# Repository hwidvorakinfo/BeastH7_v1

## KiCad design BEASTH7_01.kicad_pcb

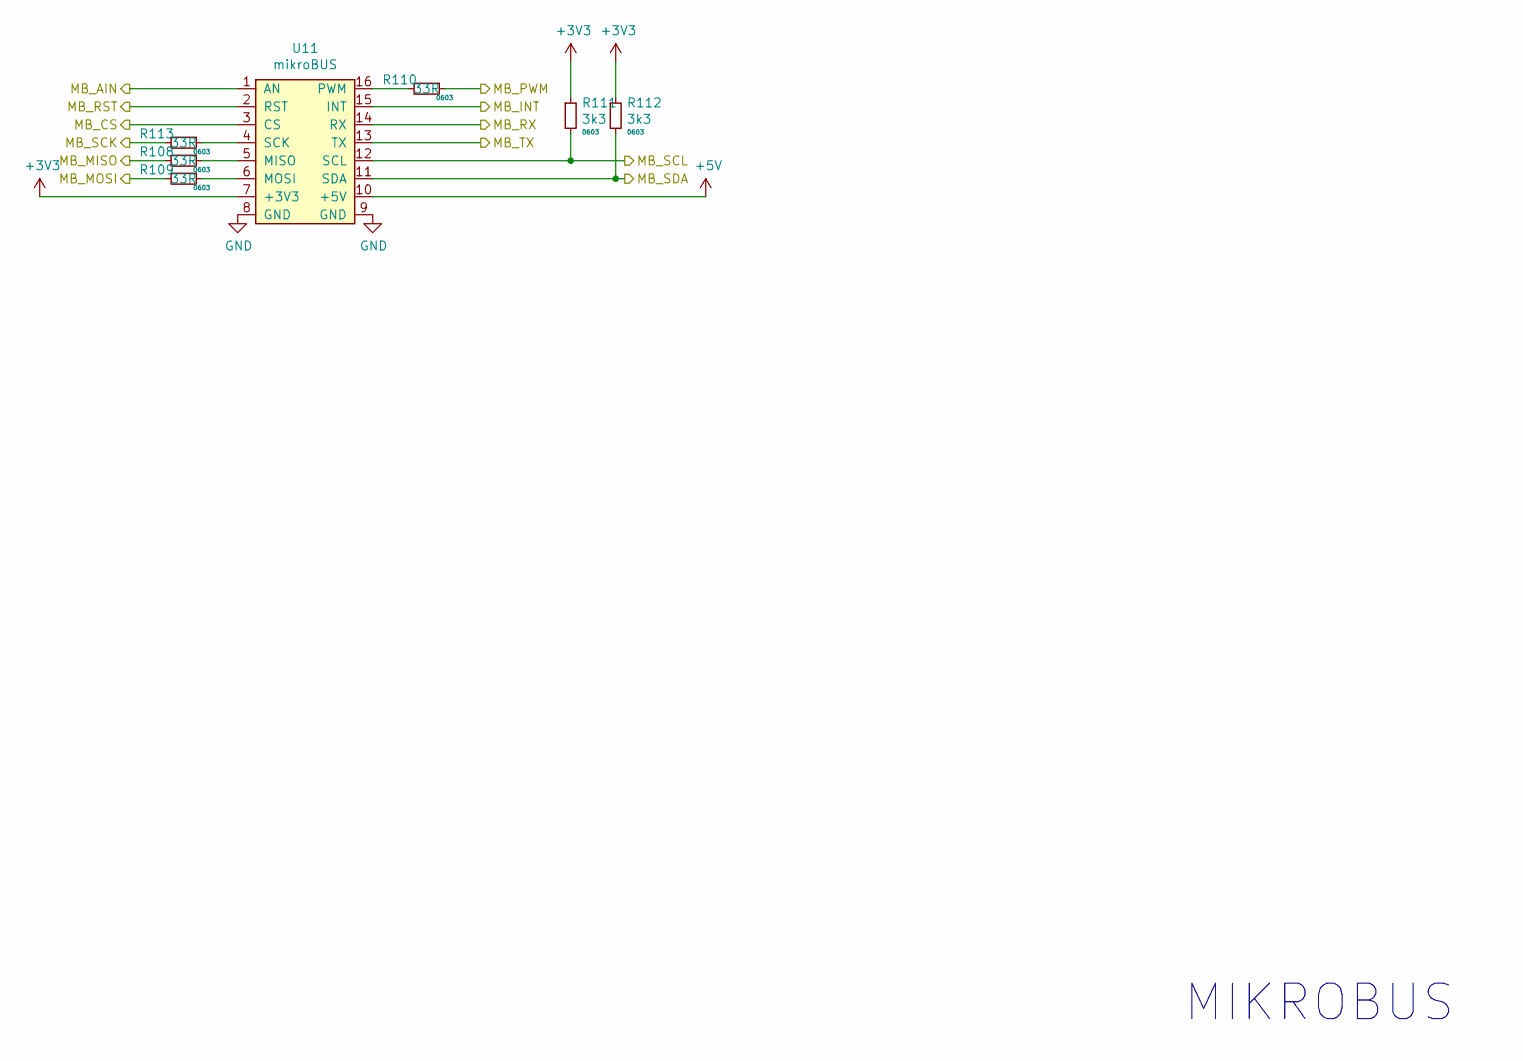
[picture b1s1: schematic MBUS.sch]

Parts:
R108, R109, R110, R113: 33R; R_0603_1608Metric
R111, R112: 3k3; R_0603_1608Metric
U11: mikroBUS

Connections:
+3V3: R111.1, R112.1, U11.7 (+3V3); also elsewhere on the board
+5V: U11.10 (+5V); also elsewhere on the board
/MCU/INPUT3: U11.1 (AN); also elsewhere on the board
/MCU/MB_CS: U11.3 (CS); also elsewhere on the board
/MCU/MB_INT: U11.15 (INT); also elsewhere on the board
/MCU/MB_MISO: R108.2; also elsewhere on the board
/MCU/MB_MOSI: R109.2; also elsewhere on the board
/MCU/MB_PWM: R110.1; also elsewhere on the board
/MCU/MB_RST: U11.2 (RST); also elsewhere on the board
/MCU/MB_RX: U11.14 (RX); also elsewhere on the board
/MCU/MB_SCK: R113.2; also elsewhere on the board
/MCU/MB_SCL: R111.2, U11.12 (SCL); also elsewhere on the board
/MCU/MB_SDA: R112.2, U11.11 (SDA); also elsewhere on the board
/MCU/MB_TX: U11.13 (TX); also elsewhere on the board
GND: U11.8 (GND), U11.9 (GND); also elsewhere on the board
unnamed: R108.1, U11.5 (MISO)
unnamed: R109.1, U11.6 (MOSI)
unnamed: R110.2, U11.16 (PWM)
unnamed: R113.1, U11.4 (SCK)

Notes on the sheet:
MIKROBUS

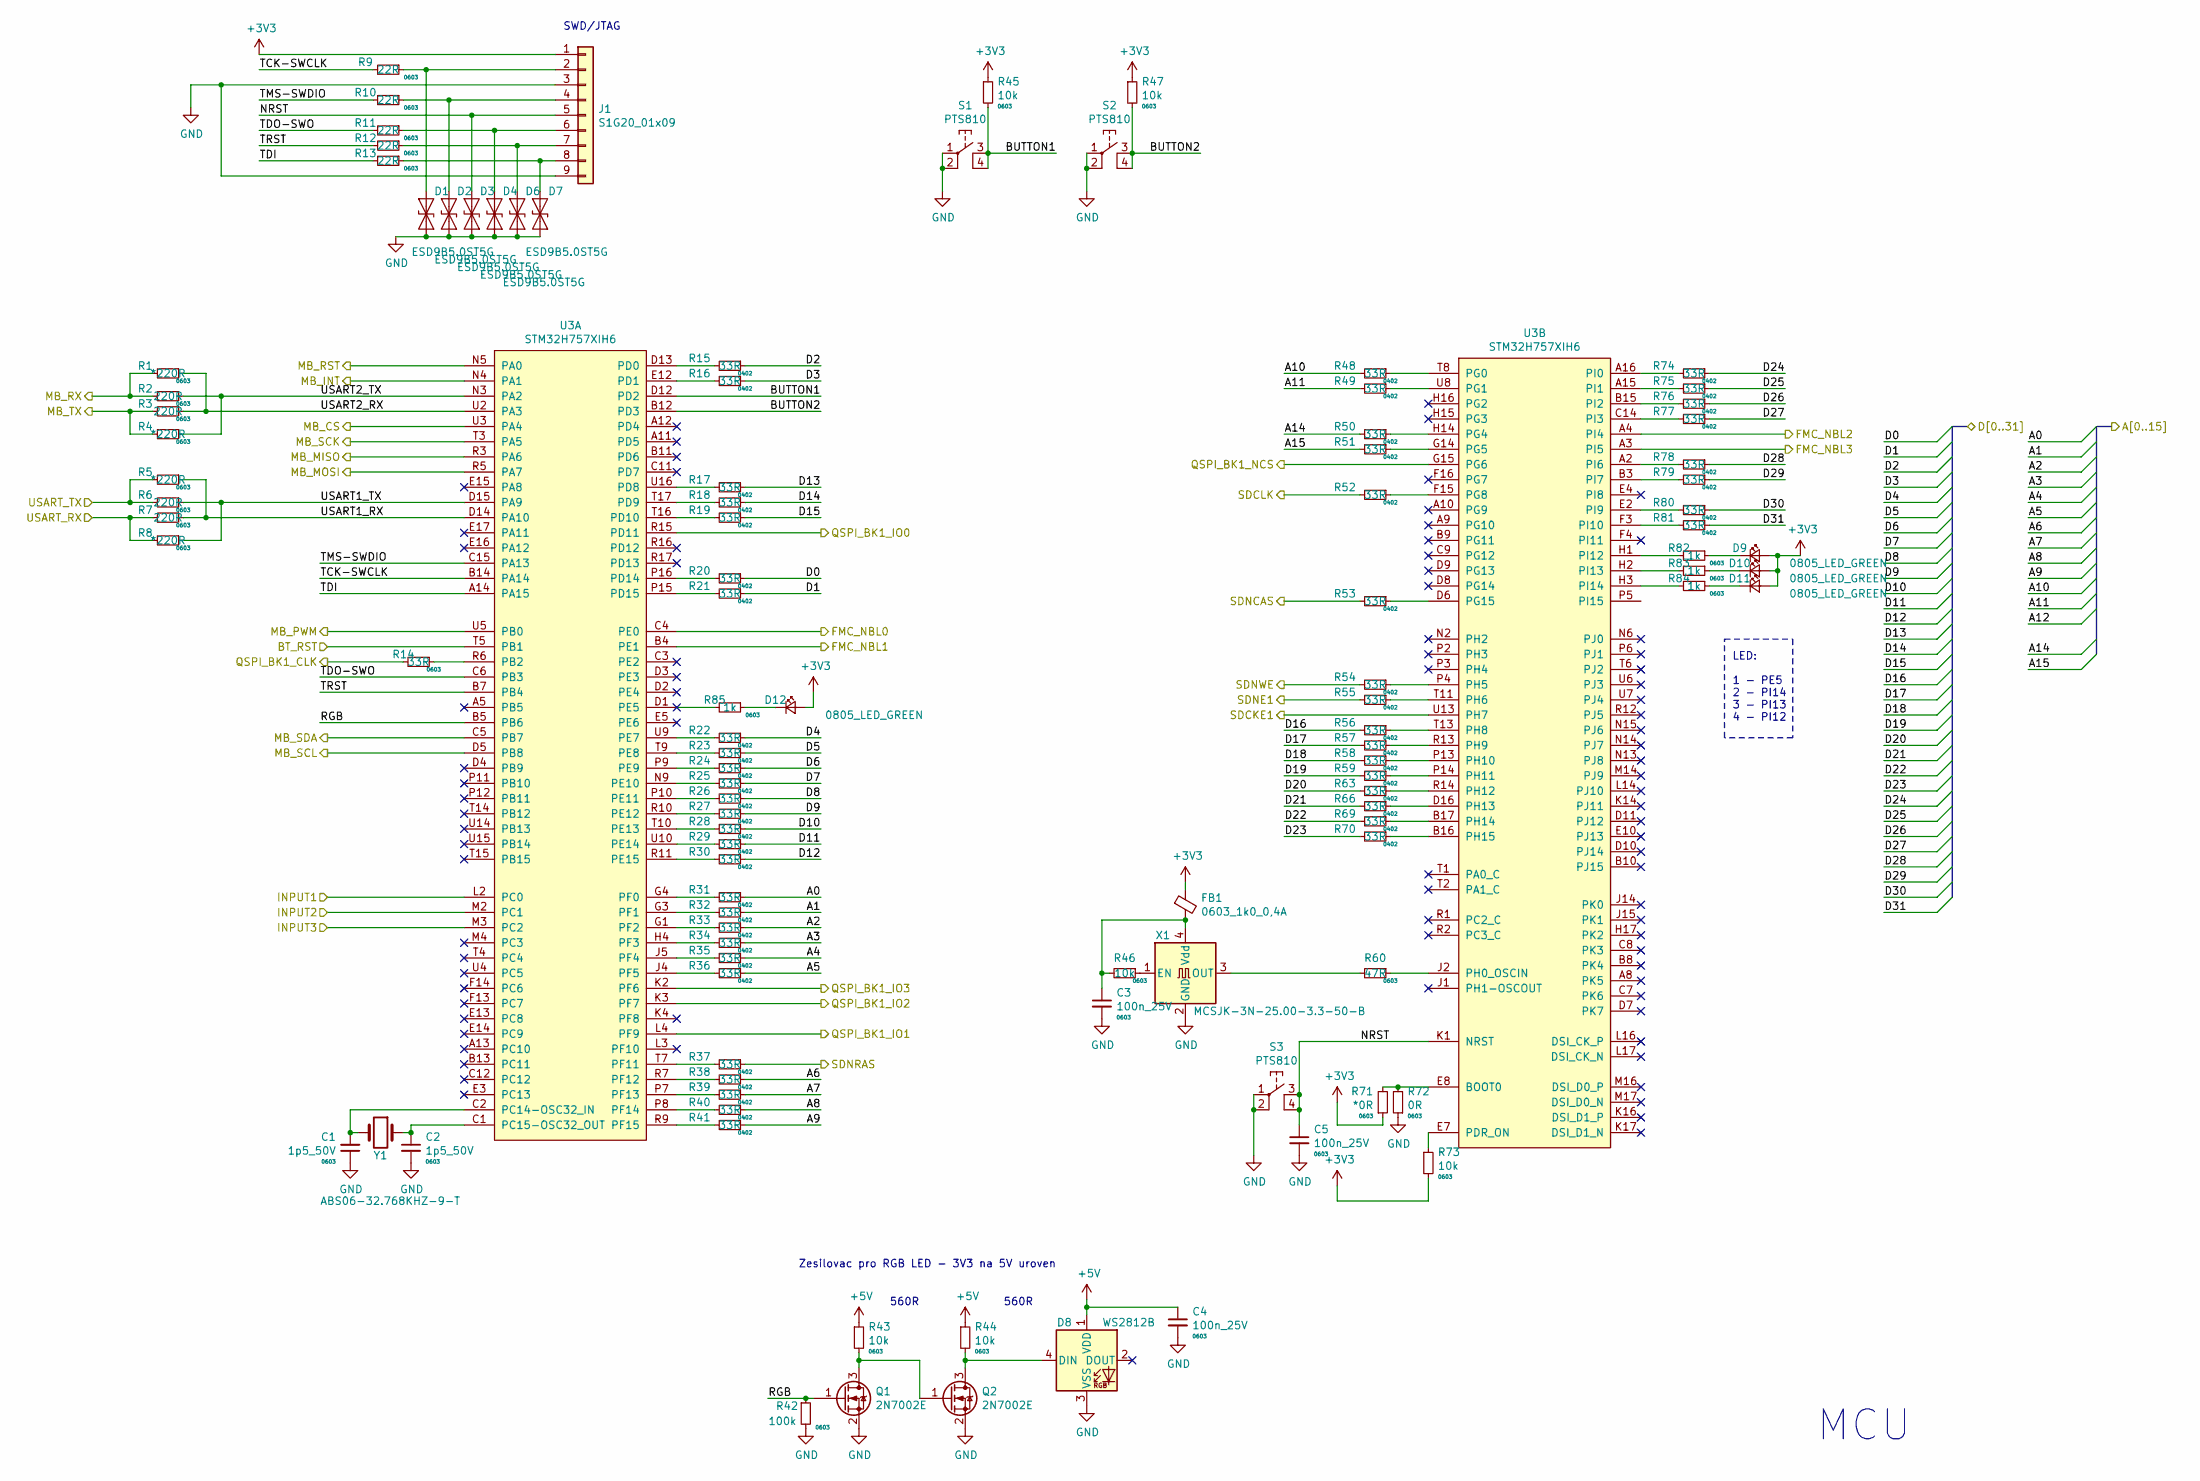
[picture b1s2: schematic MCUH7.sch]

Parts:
C1, C2: 1p5_50V; C_0603_1608Metric
C3, C4, C5: 100n_25V; C_0603_1608Metric
D1, D2, D3, D4, D6, D7: ESD9B5.0ST5G; D_0402_1005Metric
D8: WS2812B; WS2812B_PLCC4_5.0x5.0mm_P3.2mm
D9, D10, D11, D12: 0805_LED_GREEN; D_0805_2012Metric
FB1: 0603_1k0_0,4A; R_0603_1608Metric
J1: S1G20_01x09; PinHeader_1x09_P2.54mm_Vertical
Q1, Q2: 2N7002E; SOT-23
R1, R4, R5, R8: *220R; R_0603_1608Metric
R2, R3, R6, R7: 220R; R_0603_1608Metric
R9, R10, R11, R12, R13: 22R; R_0603_1608Metric
R14: 33R; R_0603_1608Metric
R15, R16, R17, R18, R19, R20, R21, R22, R23, R24, R25, R26, R27, R28, R29, R30, R31, R32, R33, R34, R35, R36, R37, R38, R39, R40, R41, R48, R49, R50, R51, R52, R53, R54, R55, R56, R57, R58, R59, R63, R66, R69, R70, R74, R75, R76, R77, R78, R79, R80, R81: 33R; R_0402_1005Metric
R42: 100k; R_0603_1608Metric
R43, R44, R45, R46, R47, R73: 10k; R_0603_1608Metric
R60: 47R; R_0603_1608Metric
R71: *0R; R_0603_1608Metric
R72: 0R; R_0603_1608Metric
R82, R83, R84, R85: 1k; R_0603_1608Metric
S1, S2, S3: PTS810; MIKROSPINAC_PTS810
U3: STM32H757XIH6; TFBGA-265_14x14mm_Layout17x17_P0.8mm
X1: MCSJK-3N-25.00-3.3-50-B; Oscillator_SMD_Abracon_ASE-4Pin_3.2x2.5mm
Y1: ABS06-32.768KHZ-9-T; Crystal_SMD_2012-2Pin_2.0x1.2mm_HandSoldering

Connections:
+3V3: D9.2 (A), D10.2 (A), D11.2 (A), D12.2 (A), FB1.1, J1.1, R45.1, R47.1, R71.1, R73.2; also elsewhere on the board
+5V: C4.1, D8.1 (VDD), R43.1, R44.1; also elsewhere on the board
/ADC Vstupy/INPUT1: U3.L2 (PC0); also elsewhere on the board
/ADC Vstupy/INPUT2: U3.M2 (PC1); also elsewhere on the board
/Bluetooth/BT_RST: U3.T5 (PB1); also elsewhere on the board
/MCU/A0: R31.1; also elsewhere on the board
/MCU/A1: R32.1; also elsewhere on the board
/MCU/A2: R33.1; also elsewhere on the board
/MCU/A3: R34.1; also elsewhere on the board
/MCU/A4: R35.1; also elsewhere on the board
/MCU/A5: R36.1; also elsewhere on the board
/MCU/A6: R38.1; also elsewhere on the board
/MCU/A7: R39.1; also elsewhere on the board
/MCU/A8: R40.1; also elsewhere on the board
/MCU/A9: R41.1; also elsewhere on the board
/MCU/A10: R48.2; also elsewhere on the board
/MCU/A11: R49.2; also elsewhere on the board
/MCU/A14: R50.2; also elsewhere on the board
/MCU/A15: R51.2; also elsewhere on the board
/MCU/BUTTON1: R45.2, S1.3, S1.4, U3.D12 (PD2)
/MCU/BUTTON2: R47.2, S2.3, S2.4, U3.B12 (PD3)
/MCU/D0: R20.1; also elsewhere on the board
/MCU/D1: R21.1; also elsewhere on the board
/MCU/D2: R15.1; also elsewhere on the board
/MCU/D3: R16.1; also elsewhere on the board
/MCU/D4: R22.1; also elsewhere on the board
/MCU/D5: R23.1; also elsewhere on the board
/MCU/D6: R24.1; also elsewhere on the board
/MCU/D7: R25.1; also elsewhere on the board
/MCU/D8: R26.1; also elsewhere on the board
/MCU/D9: R27.1; also elsewhere on the board
/MCU/D10: R28.1; also elsewhere on the board
/MCU/D11: R29.1; also elsewhere on the board
/MCU/D12: R30.1; also elsewhere on the board
/MCU/D13: R17.1; also elsewhere on the board
/MCU/D14: R18.1; also elsewhere on the board
/MCU/D15: R19.1; also elsewhere on the board
/MCU/D16: R56.2; also elsewhere on the board
/MCU/D17: R57.2; also elsewhere on the board
/MCU/D18: R58.2; also elsewhere on the board
/MCU/D19: R59.2; also elsewhere on the board
/MCU/D20: R63.2; also elsewhere on the board
/MCU/D21: R66.2; also elsewhere on the board
/MCU/D22: R69.2; also elsewhere on the board
/MCU/D23: R70.2; also elsewhere on the board
/MCU/D24: R74.1; also elsewhere on the board
/MCU/D25: R75.1; also elsewhere on the board
/MCU/D26: R76.1; also elsewhere on the board
/MCU/D27: R77.1; also elsewhere on the board
/MCU/D28: R78.1; also elsewhere on the board
/MCU/D29: R79.1; also elsewhere on the board
/MCU/D30: R80.1; also elsewhere on the board
/MCU/D31: R81.1; also elsewhere on the board
/MCU/FMC_NBL0: U3.C4 (PE0); also elsewhere on the board
/MCU/FMC_NBL1: U3.B4 (PE1); also elsewhere on the board
/MCU/FMC_NBL2: U3.A4 (PI4); also elsewhere on the board
/MCU/FMC_NBL3: U3.A3 (PI5); also elsewhere on the board
/MCU/INPUT3: U3.M3 (PC2); also elsewhere on the board
/MCU/MB_CS: U3.U3 (PA4); also elsewhere on the board
/MCU/MB_INT: U3.N4 (PA1); also elsewhere on the board
/MCU/MB_MISO: U3.R3 (PA6); also elsewhere on the board
/MCU/MB_MOSI: U3.R5 (PA7); also elsewhere on the board
/MCU/MB_PWM: U3.U5 (PB0); also elsewhere on the board
/MCU/MB_RST: U3.N5 (PA0); also elsewhere on the board
/MCU/MB_RX: R1.2, R2.2; also elsewhere on the board
/MCU/MB_SCK: U3.T3 (PA5); also elsewhere on the board
/MCU/MB_SCL: U3.D5 (PB8); also elsewhere on the board
/MCU/MB_SDA: U3.C5 (PB7); also elsewhere on the board
/MCU/MB_TX: R3.2, R4.2; also elsewhere on the board
/MCU/NRST: C5.1, D3.1 (A1), J1.5, S3.3, S3.4, U3.K1 (NRST)
/MCU/QSPI_BK1_CLK: R14.2; also elsewhere on the board
/MCU/QSPI_BK1_IO0: U3.R15 (PD11); also elsewhere on the board
/MCU/QSPI_BK1_IO1: U3.L4 (PF9); also elsewhere on the board
/MCU/QSPI_BK1_IO2: U3.K3 (PF7); also elsewhere on the board
/MCU/QSPI_BK1_IO3: U3.K2 (PF6); also elsewhere on the board
/MCU/QSPI_BK1_NCS: U3.G15 (PG6); also elsewhere on the board
/MCU/RGB: Q1.1 (G), R42.1, U3.B5 (PB6)
/MCU/SDCKE1: U3.U13 (PH7); also elsewhere on the board
/MCU/SDCLK: R52.2; also elsewhere on the board
/MCU/SDNCAS: R53.2; also elsewhere on the board
/MCU/SDNE1: R55.2; also elsewhere on the board
/MCU/SDNRAS: R37.1; also elsewhere on the board
/MCU/SDNWE: R54.2; also elsewhere on the board
/MCU/TCK-SWCLK: R9.2, U3.B14 (PA14)
/MCU/TDI: R13.2, U3.A14 (PA15)
/MCU/TDO-SWO: R11.2, U3.C6 (PB3)
/MCU/TMS-SWDIO: R10.2, U3.C15 (PA13)
/MCU/TRST: R12.2, U3.B7 (PB4)
/MCU/USART1_RX: R5.1, R7.1, U3.D14 (PA10)
/MCU/USART1_TX: R6.1, R8.1, U3.D15 (PA9)
/MCU/USART2_RX: R1.1, R3.1, U3.U2 (PA3)
/MCU/USART2_TX: R2.1, R4.1, U3.N3 (PA2)
/USB-UART/RXD: R5.2, R6.2; also elsewhere on the board
/USB-UART/TXD: R7.2, R8.2; also elsewhere on the board
GND: C1.1, C2.2, C3.2, C4.2, C5.2, D1.2 (A2), D2.2 (A2), D3.2 (A2), D4.2 (A2), D6.2 (A2), D7.2 (A2), D8.3 (VSS), J1.3, J1.9, Q1.2 (S), Q2.2 (S), R42.2, R72.1, S1.1, S1.2, S2.1, S2.2, S3.1, S3.2, X1.2 (GND); also elsewhere on the board
unnamed: C1.2, U3.C2 (PC14-OSC32_IN), Y1.2
unnamed: C2.1, U3.C1 (PC15-OSC32_OUT), Y1.1
unnamed: C3.1, FB1.2, R46.2, X1.4 (Vdd)
unnamed: D1.1 (A1), J1.2, R9.1
unnamed: D2.1 (A1), J1.4, R10.1
unnamed: D4.1 (A1), J1.6, R11.1
unnamed: D6.1 (A1), J1.7, R12.1
unnamed: D7.1 (A1), J1.8, R13.1
unnamed: D8.4 (DIN), Q2.3 (D), R44.2
unnamed: D9.1 (K), R82.1
unnamed: D10.1 (K), R83.1
unnamed: D11.1 (K), R84.1
unnamed: D12.1 (K), R85.1
unnamed: Q1.3 (D), Q2.1 (G), R43.2
unnamed: R14.1, U3.R6 (PB2)
unnamed: R15.2, U3.D13 (PD0)
unnamed: R16.2, U3.E12 (PD1)
unnamed: R17.2, U3.U16 (PD8)
unnamed: R18.2, U3.T17 (PD9)
unnamed: R19.2, U3.T16 (PD10)
unnamed: R20.2, U3.P16 (PD14)
unnamed: R21.2, U3.P15 (PD15)
unnamed: R22.2, U3.U9 (PE7)
unnamed: R23.2, U3.T9 (PE8)
unnamed: R24.2, U3.P9 (PE9)
unnamed: R25.2, U3.N9 (PE10)
unnamed: R26.2, U3.P10 (PE11)
unnamed: R27.2, U3.R10 (PE12)
unnamed: R28.2, U3.T10 (PE13)
unnamed: R29.2, U3.U10 (PE14)
unnamed: R30.2, U3.R11 (PE15)
unnamed: R31.2, U3.G4 (PF0)
unnamed: R32.2, U3.G3 (PF1)
unnamed: R33.2, U3.G1 (PF2)
unnamed: R34.2, U3.H4 (PF3)
unnamed: R35.2, U3.J5 (PF4)
unnamed: R36.2, U3.J4 (PF5)
unnamed: R37.2, U3.T7 (PF11)
unnamed: R38.2, U3.R7 (PF12)
unnamed: R39.2, U3.P7 (PF13)
unnamed: R40.2, U3.P8 (PF14)
unnamed: R41.2, U3.R9 (PF15)
unnamed: R46.1, X1.1 (EN)
unnamed: R48.1, U3.T8 (PG0)
unnamed: R49.1, U3.U8 (PG1)
unnamed: R50.1, U3.H14 (PG4)
unnamed: R51.1, U3.G14 (PG5)
unnamed: R52.1, U3.F15 (PG8)
unnamed: R53.1, U3.D6 (PG15)
unnamed: R54.1, U3.P4 (PH5)
unnamed: R55.1, U3.T11 (PH6)
unnamed: R56.1, U3.T13 (PH8)
unnamed: R57.1, U3.R13 (PH9)
unnamed: R58.1, U3.P13 (PH10)
unnamed: R59.1, U3.P14 (PH11)
unnamed: R60.1, U3.J2 (PH0_OSCIN)
unnamed: R60.2, X1.3 (OUT)
unnamed: R63.1, U3.R14 (PH12)
unnamed: R66.1, U3.D16 (PH13)
unnamed: R69.1, U3.B17 (PH14)
unnamed: R70.1, U3.B16 (PH15)
unnamed: R71.2, R72.2, U3.E8 (BOOT0)
unnamed: R73.1, U3.E7 (PDR_ON)
unnamed: R74.2, U3.A16 (PI0)
unnamed: R75.2, U3.A15 (PI1)
unnamed: R76.2, U3.B15 (PI2)
unnamed: R77.2, U3.C14 (PI3)
unnamed: R78.2, U3.A2 (PI6)
unnamed: R79.2, U3.B3 (PI7)
unnamed: R80.2, U3.E2 (PI9)
unnamed: R81.2, U3.F3 (PI10)
unnamed: R82.2, U3.H1 (PI12)
unnamed: R83.2, U3.H2 (PI13)
unnamed: R84.2, U3.H3 (PI14)
unnamed: R85.2, U3.D1 (PE5)

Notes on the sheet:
Zesilovac pro RGB LED - 3V3 na 5V uroven
SWD/JTAG
MCU
LED: 1 - PE5 2 - PI14 3 - PI13 4 - PI12
560R

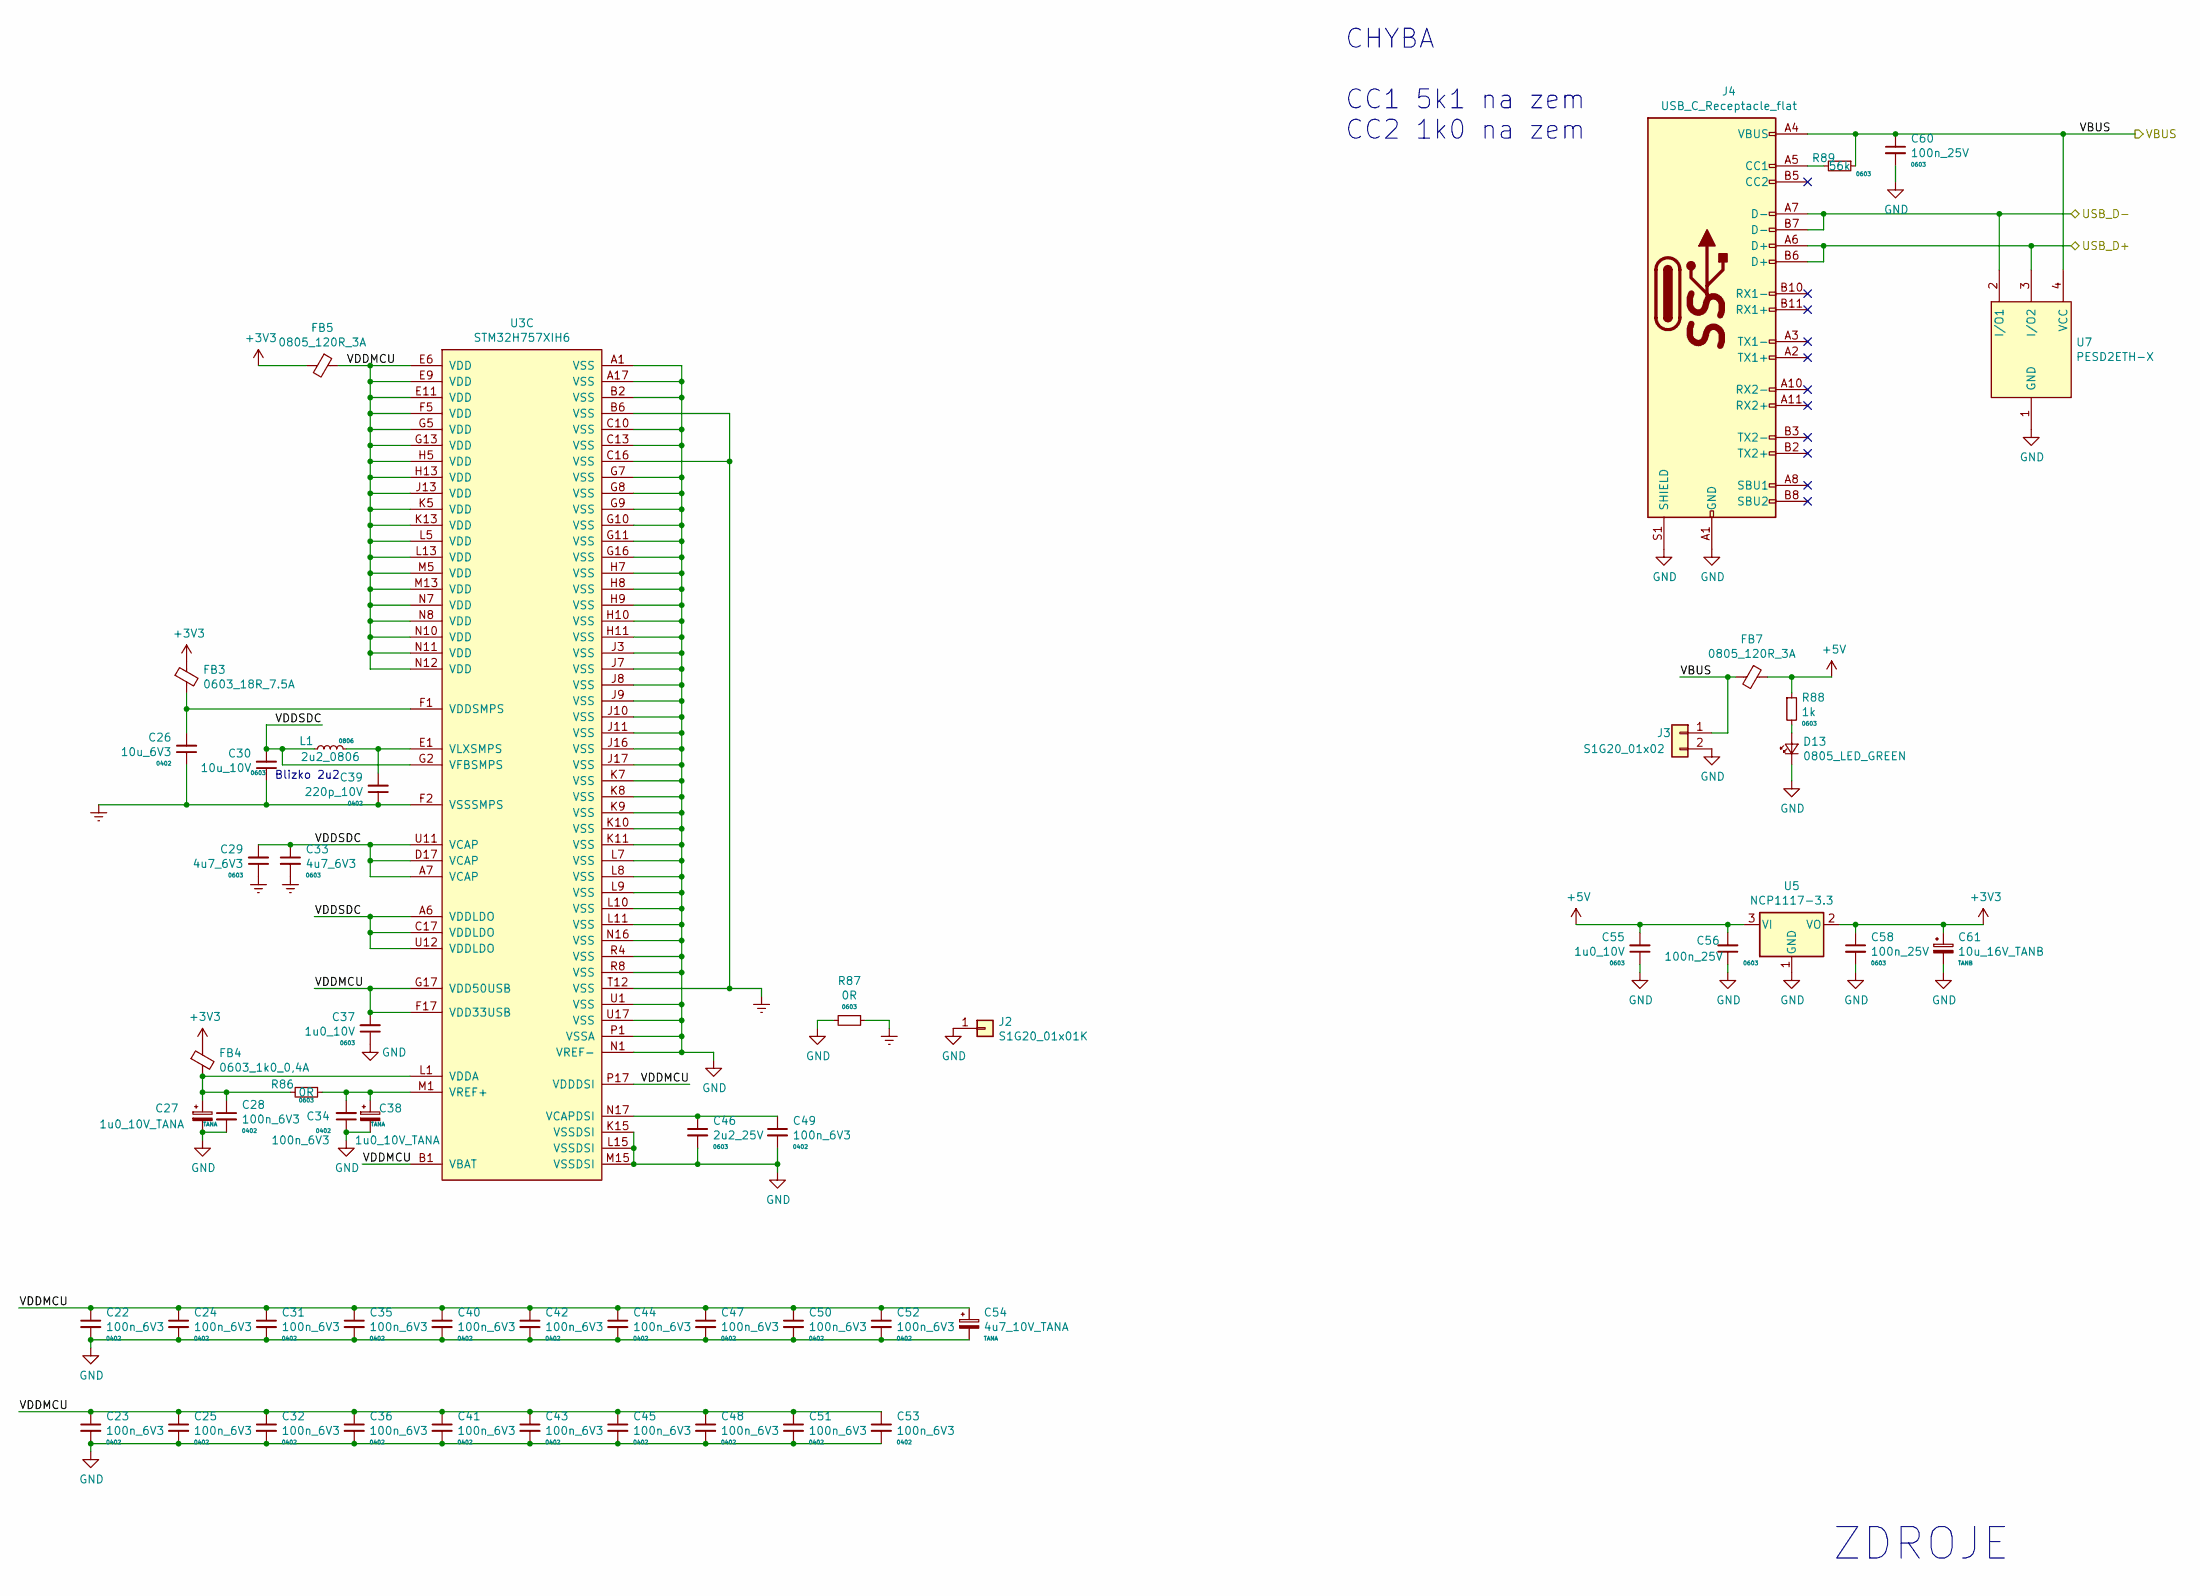
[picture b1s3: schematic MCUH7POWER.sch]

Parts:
C22, C23, C24, C25, C28, C31, C32, C34, C35, C36, C40, C41, C42, C43, C44, C45, C47, C48, C49, C50, C51, C52, C53: 100n_6V3; C_0402_1005Metric
C26: 10u_6V3; C_0402_1005Metric
C27, C38: 1u0_10V_TANA; CP_EIA-3216-18_Kemet-A
C29, C33: 4u7_6V3; C_0603_1608Metric
C30: 10u_10V; C_0603_1608Metric
C37, C55: 1u0_10V; C_0603_1608Metric
C39: 220p_10V; C_0402_1005Metric
C46: 2u2_25V; C_0603_1608Metric
C54: 4u7_10V_TANA; CP_EIA-3216-18_Kemet-A
C56, C58, C60: 100n_25V; C_0603_1608Metric
C61: 10u_16V_TANB; CP_EIA-3528-21_Kemet-B
D13: 0805_LED_GREEN; D_0805_2012Metric
FB3: 0603_18R_7.5A; R_0603_1608Metric
FB4: 0603_1k0_0,4A; R_0603_1608Metric
FB5, FB7: 0805_120R_3A; R_0805_2012Metric
J2: S1G20_01x01K; S1G20_1x1_kulaty
J3: S1G20_01x02; PinHeader_1x02_P2.54mm_Vertical
J4: USB_C_Receptacle_flat; USB-C_632723100011_1MM
L1: 2u2_0806; R_0805_2012Metric_Pad1.15x1.40mm_HandSolder
R86, R87: 0R; R_0603_1608Metric
R88: 1k; R_0603_1608Metric
R89: 56k; R_0603_1608Metric
U3: STM32H757XIH6; TFBGA-265_14x14mm_Layout17x17_P0.8mm
U5: NCP1117-3.3; SOT-223-3_TabPin2
U7: PESD2ETH-X; SOT-143

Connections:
+3V3: C58.1, C61.1, FB3.1, FB4.1, FB5.2, U5.2 (VO); also elsewhere on the board
+5V: C55.2, C56.2, FB7.1, R88.1, U5.3 (VI); also elsewhere on the board
/MCU Power/VDDMCU: C22.1, C23.1, C24.1, C25.1, C31.1, C32.1, C35.1, C36.1, C37.2, C40.1, C41.1, C42.1, C43.1, C44.1, C45.1, C47.1, C48.1, C50.1, C51.1, C52.1, C53.1, C54.1, FB5.1, U3.B1 (VBAT), U3.E6 (VDD), U3.E9 (VDD), U3.E11 (VDD), U3.F5 (VDD), U3.F17 (VDD33USB), U3.G5 (VDD), U3.G13 (VDD), U3.G17 (VDD50USB), U3.H5 (VDD), U3.H13 (VDD), U3.J13 (VDD), U3.K5 (VDD), U3.K13 (VDD), U3.L5 (VDD), U3.L13 (VDD), U3.M5 (VDD), U3.M13 (VDD), U3.N7 (VDD), U3.N8 (VDD), U3.N10 (VDD), U3.N11 (VDD), U3.N12 (VDD), U3.P17 (VDDDSI)
/MCU Power/VDDSDC: C29.2, C30.2, C33.1, L1.1, U3.A6 (VDDLDO), U3.A7 (VCAP), U3.C17 (VDDLDO), U3.D17 (VCAP), U3.G2 (VFBSMPS), U3.U11 (VCAP), U3.U12 (VDDLDO)
/USB_D+: J4.A6 (D+), J4.B6 (D+), U7.3 (I/O2); also elsewhere on the board
/USB_D-: J4.A7 (D-), J4.B7 (D-), U7.2 (I/O1); also elsewhere on the board
/VBUS: C60.1, FB7.2, J3.1, J4.A4 (VBUS), J4.A9 (VBUS), J4.B4 (VBUS), J4.B9 (VBUS), R89.1, U7.4 (VCC); also elsewhere on the board
Earth: C26.1, C29.1, C30.1, C33.2, C39.1, R87.1, U3.B6 (VSS), U3.C16 (VSS), U3.F2 (VSSSMPS), U3.T12 (VSS)
GND: C22.2, C23.2, C24.2, C25.2, C27.2, C28.2, C31.2, C32.2, C34.1, C35.2, C36.2, C37.1, C38.2, C40.2, C41.2, C42.2, C43.2, C44.2, C45.2, C46.2, C47.2, C48.2, C49.2, C50.2, C51.2, C52.2, C53.2, C54.2, C55.1, C56.1, C58.2, C60.2, C61.2, D13.1 (K), J2.1, J3.2, J4.A1 (GND), J4.A12 (GND), J4.B1 (GND), J4.B12 (GND), J4.S1 (SHIELD), R87.2, U3.A1 (VSS), U3.A17 (VSS), U3.B2 (VSS), U3.C10 (VSS), U3.C13 (VSS), U3.G7 (VSS), U3.G8 (VSS), U3.G9 (VSS), U3.G10 (VSS), U3.G11 (VSS), U3.G16 (VSS), U3.H7 (VSS), U3.H8 (VSS), U3.H9 (VSS), U3.H10 (VSS), U3.H11 (VSS), U3.J3 (VSS), U3.J7 (VSS), U3.J8 (VSS), U3.J9 (VSS), U3.J10 (VSS), U3.J11 (VSS), U3.J16 (VSS), U3.J17 (VSS), U3.K7 (VSS), U3.K8 (VSS), U3.K9 (VSS), U3.K10 (VSS), U3.K11 (VSS), U3.K15 (VSSDSI), U3.L7 (VSS), U3.L8 (VSS), U3.L9 (VSS), U3.L10 (VSS), U3.L11 (VSS), U3.L15 (VSSDSI), U3.M15 (VSSDSI), U3.N1 (VREF-), U3.N16 (VSS), U3.P1 (VSSA), U3.R4 (VSS), U3.R8 (VSS), U3.U1 (VSS), U3.U17 (VSS), U5.1 (GND), U7.1 (GND); also elsewhere on the board
unnamed: C26.2, FB3.2, U3.F1 (VDDSMPS)
unnamed: C27.1, C28.1, FB4.2, R86.2, U3.L1 (VDDA)
unnamed: C34.2, C38.1, R86.1, U3.M1 (VREF+)
unnamed: C39.2, L1.2, U3.E1 (VLXSMPS)
unnamed: C46.1, C49.1, U3.N17 (VCAPDSI)
unnamed: D13.2 (A), R88.2
unnamed: J4.A5 (CC1), R89.2

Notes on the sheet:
Blizko 2u2
ZDROJE
CHYBA CC1 5k1 na zem CC2 1k0 na zem

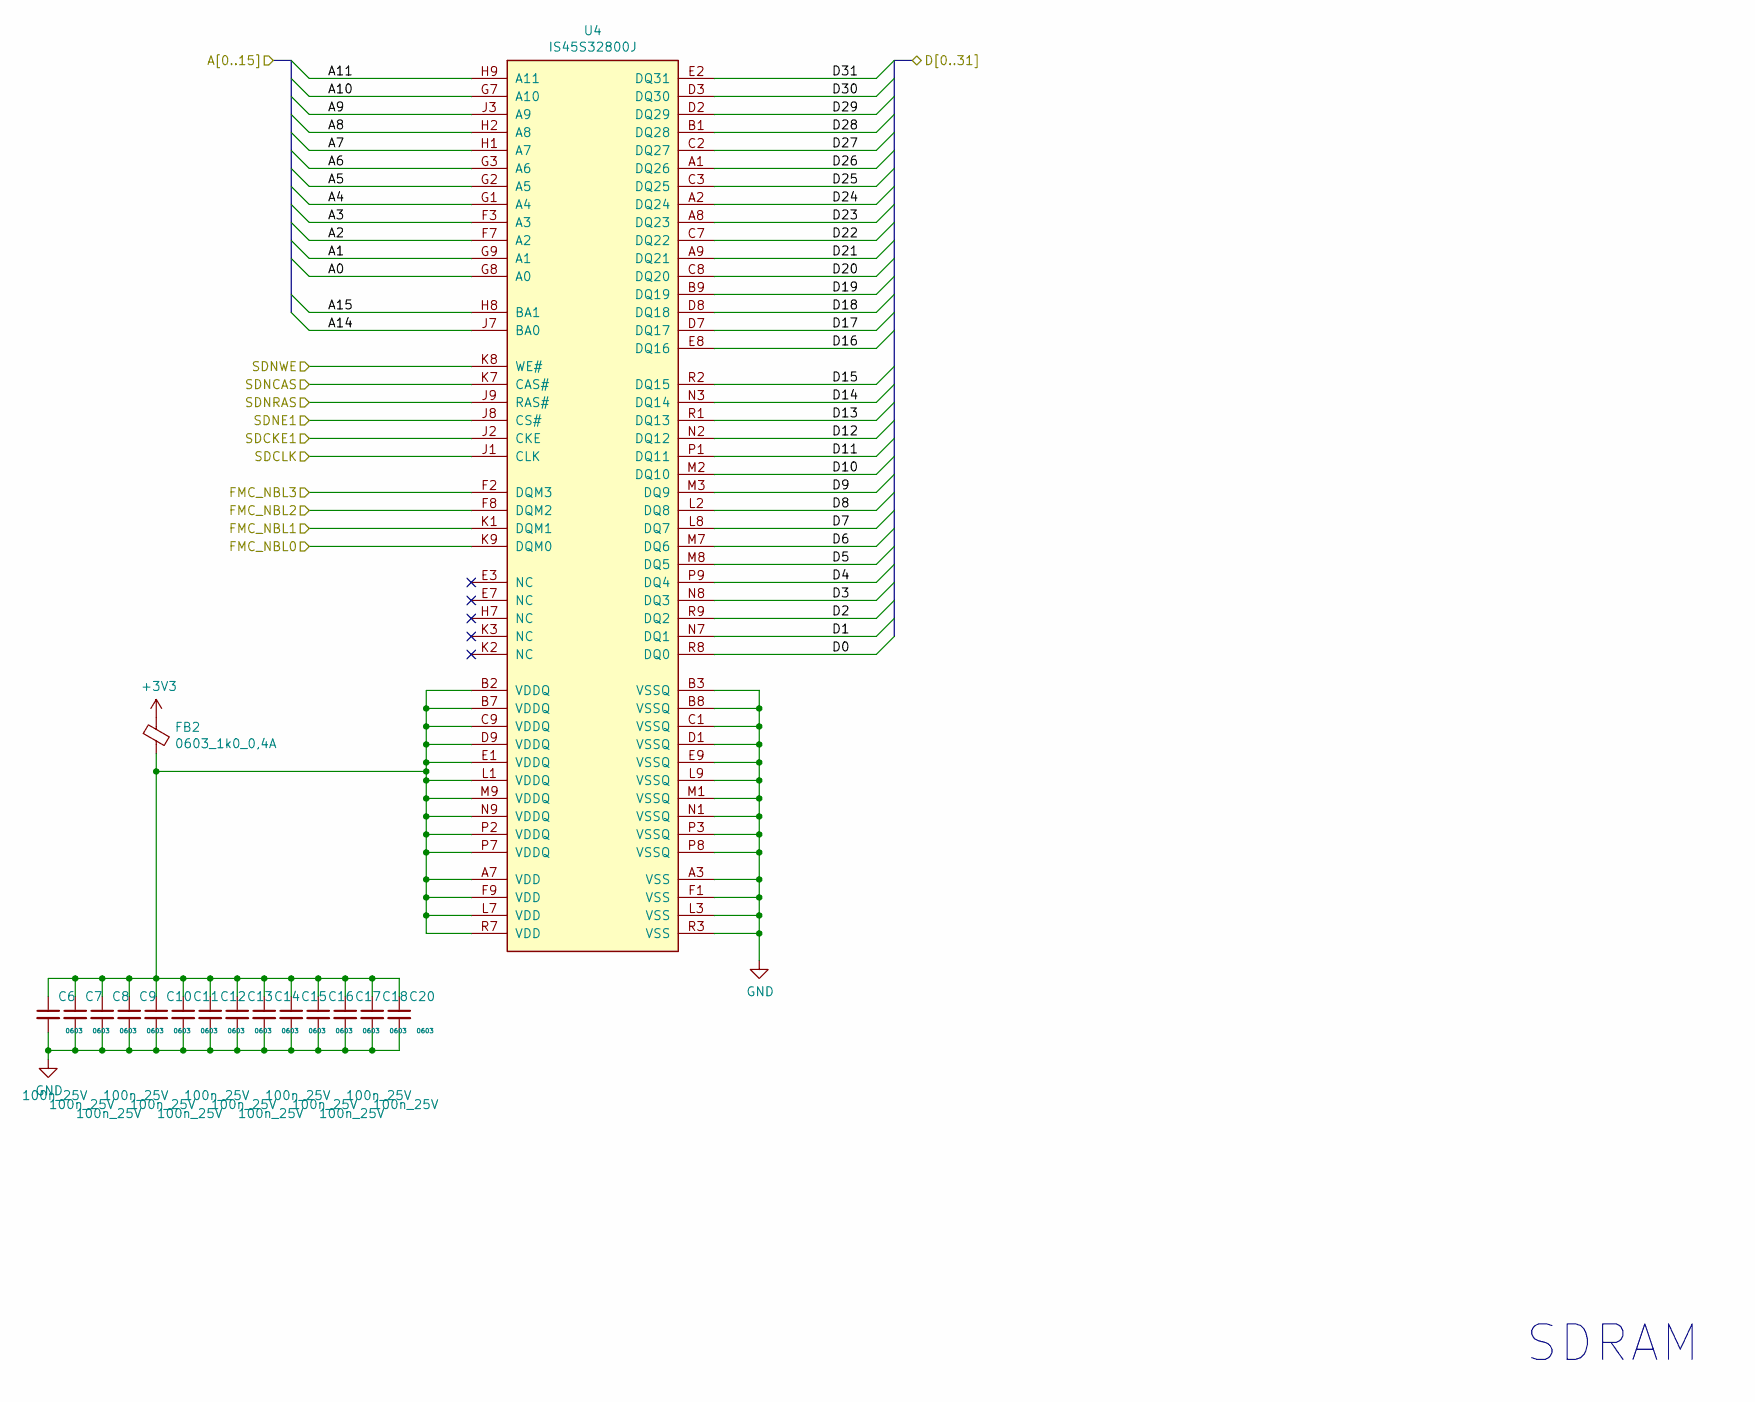
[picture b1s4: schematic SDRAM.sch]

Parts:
C6, C7, C8, C9, C10, C11, C12, C13, C14, C15, C16, C17, C18, C20: 100n_25V; C_0603_1608Metric
FB2: 0603_1k0_0,4A; R_0603_1608Metric
U4: IS45S32800J; BGA-90_8.0x13.0mm_Layout2x3x15_P0.8mm

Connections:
+3V3: FB2.1; also elsewhere on the board
/MCU/A0: U4.G8 (A0); also elsewhere on the board
/MCU/A1: U4.G9 (A1); also elsewhere on the board
/MCU/A2: U4.F7 (A2); also elsewhere on the board
/MCU/A3: U4.F3 (A3); also elsewhere on the board
/MCU/A4: U4.G1 (A4); also elsewhere on the board
/MCU/A5: U4.G2 (A5); also elsewhere on the board
/MCU/A6: U4.G3 (A6); also elsewhere on the board
/MCU/A7: U4.H1 (A7); also elsewhere on the board
/MCU/A8: U4.H2 (A8); also elsewhere on the board
/MCU/A9: U4.J3 (A9); also elsewhere on the board
/MCU/A10: U4.G7 (A10); also elsewhere on the board
/MCU/A11: U4.H9 (A11); also elsewhere on the board
/MCU/A14: U4.J7 (BA0); also elsewhere on the board
/MCU/A15: U4.H8 (BA1); also elsewhere on the board
/MCU/D0: U4.R8 (DQ0); also elsewhere on the board
/MCU/D1: U4.N7 (DQ1); also elsewhere on the board
/MCU/D2: U4.R9 (DQ2); also elsewhere on the board
/MCU/D3: U4.N8 (DQ3); also elsewhere on the board
/MCU/D4: U4.P9 (DQ4); also elsewhere on the board
/MCU/D5: U4.M8 (DQ5); also elsewhere on the board
/MCU/D6: U4.M7 (DQ6); also elsewhere on the board
/MCU/D7: U4.L8 (DQ7); also elsewhere on the board
/MCU/D8: U4.L2 (DQ8); also elsewhere on the board
/MCU/D9: U4.M3 (DQ9); also elsewhere on the board
/MCU/D10: U4.M2 (DQ10); also elsewhere on the board
/MCU/D11: U4.P1 (DQ11); also elsewhere on the board
/MCU/D12: U4.N2 (DQ12); also elsewhere on the board
/MCU/D13: U4.R1 (DQ13); also elsewhere on the board
/MCU/D14: U4.N3 (DQ14); also elsewhere on the board
/MCU/D15: U4.R2 (DQ15); also elsewhere on the board
/MCU/D16: U4.E8 (DQ16); also elsewhere on the board
/MCU/D17: U4.D7 (DQ17); also elsewhere on the board
/MCU/D18: U4.D8 (DQ18); also elsewhere on the board
/MCU/D19: U4.B9 (DQ19); also elsewhere on the board
/MCU/D20: U4.C8 (DQ20); also elsewhere on the board
/MCU/D21: U4.A9 (DQ21); also elsewhere on the board
/MCU/D22: U4.C7 (DQ22); also elsewhere on the board
/MCU/D23: U4.A8 (DQ23); also elsewhere on the board
/MCU/D24: U4.A2 (DQ24); also elsewhere on the board
/MCU/D25: U4.C3 (DQ25); also elsewhere on the board
/MCU/D26: U4.A1 (DQ26); also elsewhere on the board
/MCU/D27: U4.C2 (DQ27); also elsewhere on the board
/MCU/D28: U4.B1 (DQ28); also elsewhere on the board
/MCU/D29: U4.D2 (DQ29); also elsewhere on the board
/MCU/D30: U4.D3 (DQ30); also elsewhere on the board
/MCU/D31: U4.E2 (DQ31); also elsewhere on the board
/MCU/FMC_NBL0: U4.K9 (DQM0); also elsewhere on the board
/MCU/FMC_NBL1: U4.K1 (DQM1); also elsewhere on the board
/MCU/FMC_NBL2: U4.F8 (DQM2); also elsewhere on the board
/MCU/FMC_NBL3: U4.F2 (DQM3); also elsewhere on the board
/MCU/SDCKE1: U4.J2 (CKE); also elsewhere on the board
/MCU/SDCLK: U4.J1 (CLK); also elsewhere on the board
/MCU/SDNCAS: U4.K7 (CAS#); also elsewhere on the board
/MCU/SDNE1: U4.J8 (CS#); also elsewhere on the board
/MCU/SDNRAS: U4.J9 (RAS#); also elsewhere on the board
/MCU/SDNWE: U4.K8 (WE#); also elsewhere on the board
GND: C6.2, C7.2, C8.2, C9.2, C10.2, C11.2, C12.2, C13.2, C14.2, C15.2, C16.2, C17.2, C18.2, C20.2, U4.A3 (VSS), U4.B3 (VSSQ), U4.B8 (VSSQ), U4.C1 (VSSQ), U4.D1 (VSSQ), U4.E9 (VSSQ), U4.F1 (VSS), U4.L3 (VSS), U4.L9 (VSSQ), U4.M1 (VSSQ), U4.N1 (VSSQ), U4.P3 (VSSQ), U4.P8 (VSSQ), U4.R3 (VSS); also elsewhere on the board
unnamed: C6.1, C7.1, C8.1, C9.1, C10.1, C11.1, C12.1, C13.1, C14.1, C15.1, C16.1, C17.1, C18.1, C20.1, FB2.2, U4.A7 (VDD), U4.B2 (VDDQ), U4.B7 (VDDQ), U4.C9 (VDDQ), U4.D9 (VDDQ), U4.E1 (VDDQ), U4.F9 (VDD), U4.L1 (VDDQ), U4.L7 (VDD), U4.M9 (VDDQ), U4.N9 (VDDQ), U4.P2 (VDDQ), U4.P7 (VDDQ), U4.R7 (VDD)

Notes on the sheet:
SDRAM
